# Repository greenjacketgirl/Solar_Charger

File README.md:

# Solar Charger Project

**Introduction** | This project was done in fullfillment of the requirments for Walla Walla University's Power Electronics class (ENGR 460) taught by [Dr. Rob Frohne](https://github.com/frohro). I chose to use Texas Instruments' BQ24650 integrated circuit as the voltage regular between a 11V solar panel and 2s 7.4V lipo. The aim was for the solar panel to charge the lipo battery at 0.5A so as to charge the battery at a standard pace while keeping the pace slow enough that the battery would not be damaged. For more details on the theory used by the charger IC, design specifications, user manual, and more - please reference the [Wiki](https://github.com/greenjacketgirl/Solar_Charger/wiki).

**Navigation** |This repository has content in the [Code](https://github.com/greenjacketgirl/Solar_Charger), [Issues](https://github.com/greenjacketgirl/Solar_Charger/issues), and [Wiki](https://github.com/greenjacketgirl/Solar_Charger/wiki) tabs.The Code section has 1 primary folder - "Solar-Charger" which contains two other folders, "Documentation" and "Kicad". The documentation folder contains stepping stone write ups and research on topics related to the issue as well as my power point presentation on the project. The Kicad folder contains the kicad files, revisions 1 and 2. Note the revisions when you are referencing them. The Wiki page contains the bulk of the documentation for this project which includes, but is not limited to the results, pcb and schematic design motives, specifiations, and objectives for the project. 

**Credits** | This project was chosen and directed by myself. However, I had professional support from my professor [Dr. Rob Frohne](https://github.com/frohro) as well as assistance from the application engineeers at texas instruments. 

**Project Status** | At the current time, the project does not fully work. While the charger circuit does not have any fried or damaged components, it does not charge the lipo battery. The STAT 1 LED turns on, indicating "charging in progress", but no charging has taken place from what I could deduce. See the [Issues](https://github.com/greenjacketgirl/Solar_Charger/issues) page for updates on current bugs.

REV 1: 05/26/2020 Build and Test Stage PART 1 | REV 2: 06/09/2020 Buil and Test Stage PART 2

***
page created by jordyn watkins | greenjacketgirl

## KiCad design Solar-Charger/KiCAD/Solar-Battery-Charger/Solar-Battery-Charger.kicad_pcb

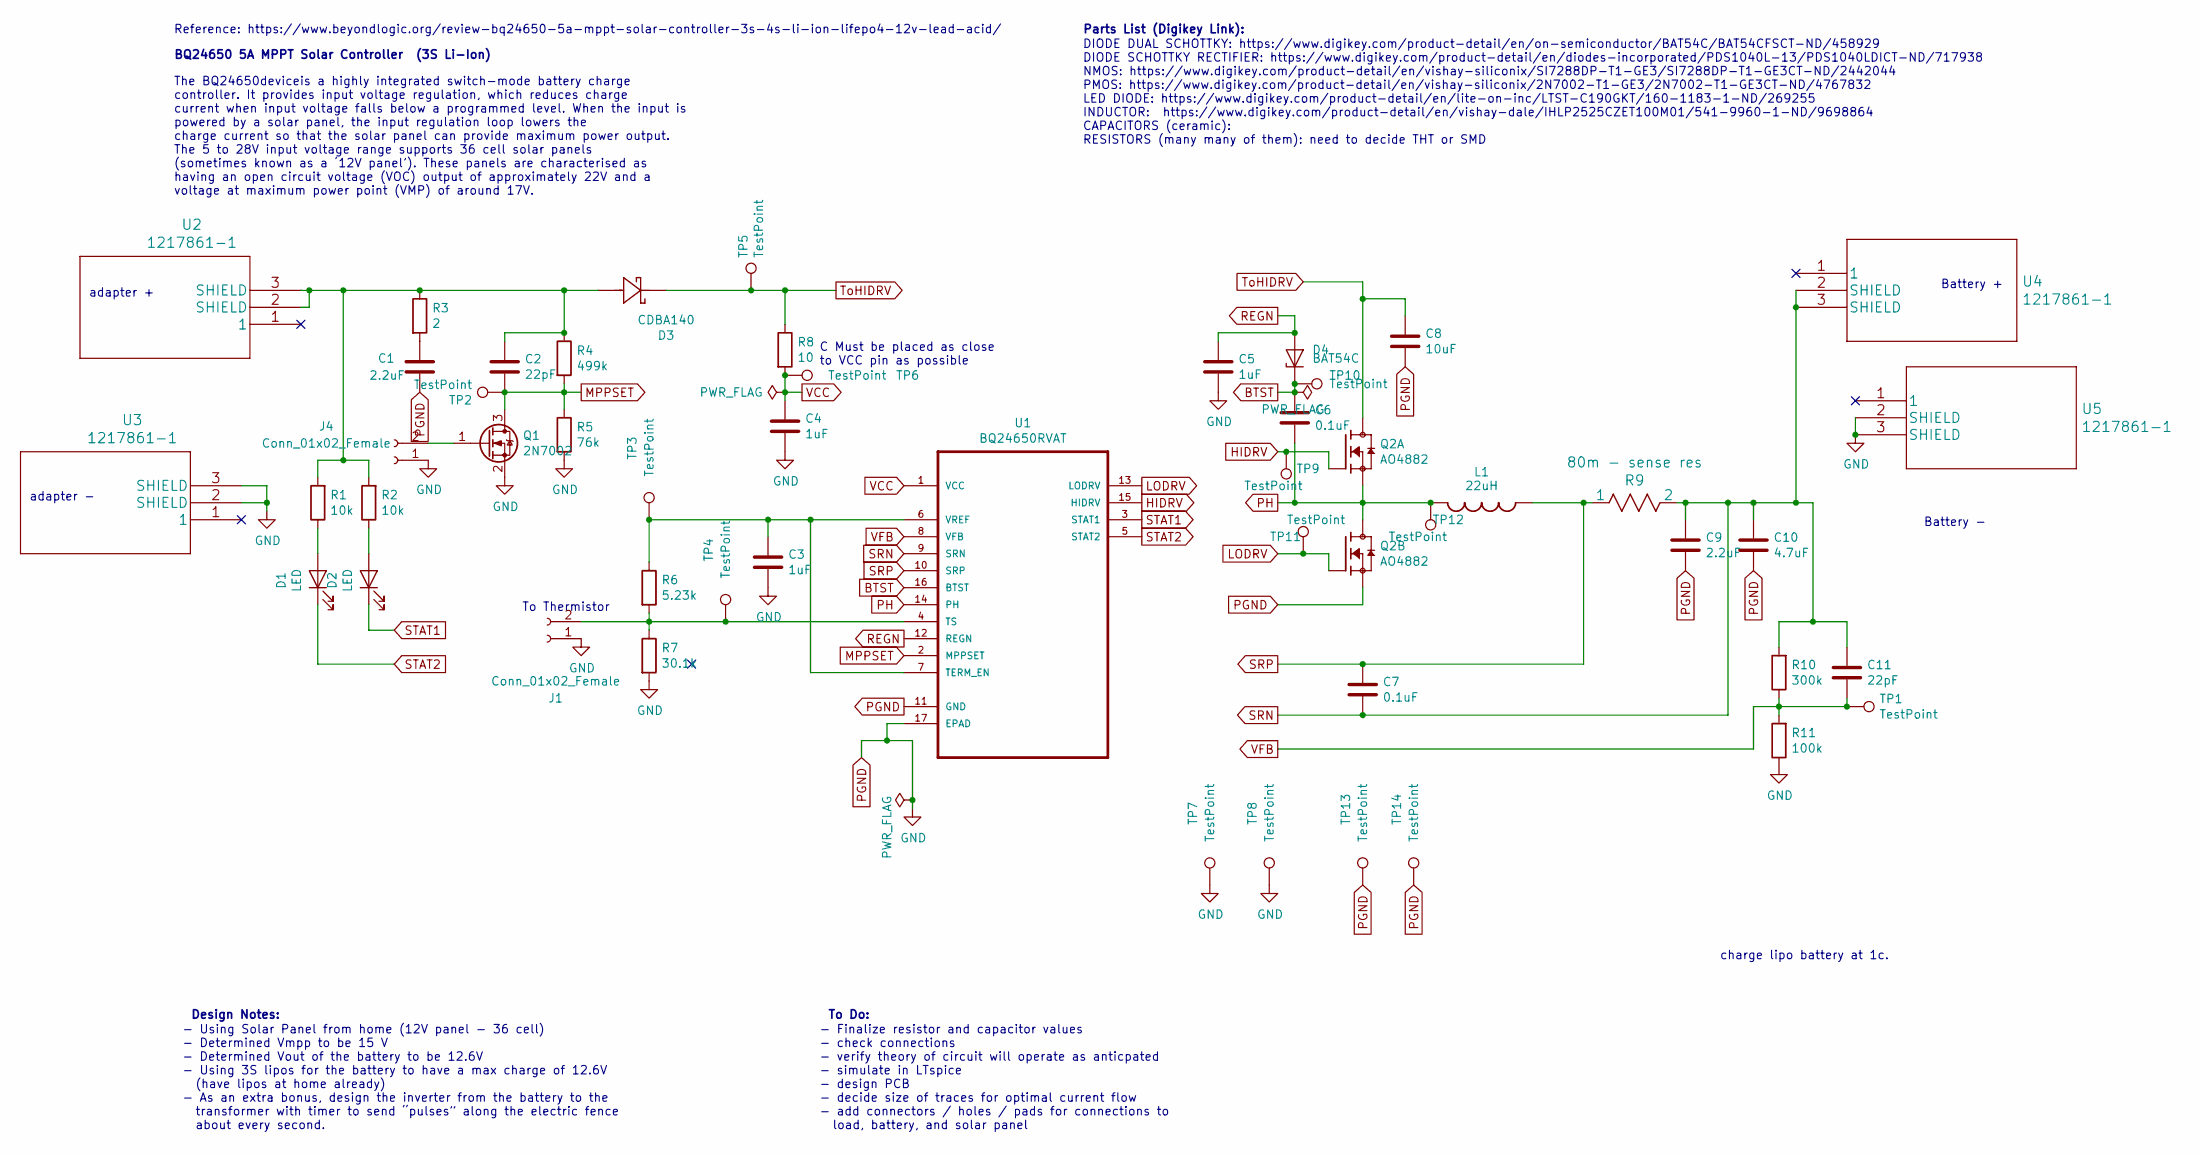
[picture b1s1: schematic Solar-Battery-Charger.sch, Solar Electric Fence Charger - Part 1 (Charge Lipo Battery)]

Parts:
C1, C9: 2.2uF; C_0805_2012Metric
C2, C11: 22pF; C_0805_2012Metric
C3, C4, C5: 1uF; C_0805_2012Metric
C6, C7: 0.1uF; C_0805_2012Metric
C8: 10uF; C_0805_2012Metric
C10: 4.7uF; C_0805_2012Metric
D1, D2: LED; D_0805_2012Metric
D3: CDBA140; CDBA140-G
D4: BAT54C; SOT-23
J1, J4: Conn_01x02_Female; PinSocket_1x02_P2.54mm_Vertical
L1: 22uH; L_0805_2012Metric
Q1: 2N7002; SOT-23
Q2: AO4882; SOIC-8_3.9x4.9mm_P1.27mm
R1, R2: 10k; R_0805_2012Metric
R3: 2; R_0805_2012Metric
R4: 499k; R_0805_2012Metric
R5: 76k; R_0805_2012Metric
R6: 5.23k; R_0805_2012Metric
R7: 30.1k; R_0805_2012Metric
R8: 10; R_0805_2012Metric
R9: 80m - sense res; R_1206_3216Metric
R10: 300k; R_0805_2012Metric
R11: 100k; R_0805_2012Metric
TP1, TP2, TP3, TP4, TP5, TP6, TP7, TP8, TP9, TP10, TP11, TP12, TP13, TP14: TestPoint; TestPoint_Loop_D1.80mm_Drill1.0mm_Beaded
U1: BQ24650RVAT; QFN50P350X350X100-17N
U2, U3, U4, U5: 1217861-1

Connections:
BTST: C6.1, D4.1 (K), TP10.1, U1.16 (BTST)
HIDRV: Q2.4 (G1), TP9.1, U1.15 (HIDRV)
LODRV: Q2.2 (G2), TP11.1, U1.13 (LODRV)
MPPSET: C2.2, Q1.3 (D), R4.2, R5.1, TP2.1, U1.2 (MPPSET)
unnamed: C1.1, R3.2
unnamed: C2.1, D3.2, R1.2, R2.2, R3.1, R4.1, U2.2 (SHIELD), U2.3 (SHIELD)
unnamed: C3.1, R6.1, TP3.1, U1.6 (VREF), U1.7 (TERM_EN)
unnamed: D1.2 (A), R1.1
unnamed: D2.2 (A), R2.1
unnamed: J1.2, R6.2, R7.1, TP4.1, U1.4 (TS)
unnamed: J4.2, Q1.1 (G)
PGND: C1.2, C3.2, C4.2, C5.2, C8.2, C9.1, C10.1, J1.1, J4.1, Q1.2 (S), Q2.1 (S2), R5.2, R7.2, R11.1, TP7.1, TP8.1, TP13.1, TP14.1, U1.11 (GND), U1.17 (EPAD), U3.2 (SHIELD), U3.3 (SHIELD), U5.2 (SHIELD), U5.3 (SHIELD)
PH: C6.2, L1.1, Q2.3 (S1), Q2.7 (D2), Q2.8 (D2), TP12.1, U1.14 (PH)
REGN: C5.1, D4.2 (A), U1.12 (REGN)
SRN: C7.1, C9.2, C10.2, C11.2, R9.2, R10.2, U1.9 (SRN), U4.2 (SHIELD), U4.3 (SHIELD)
SRP: C7.2, L1.2, R9.1, U1.10 (SRP)
STAT1: D2.1 (K), U1.3 (STAT1)
STAT2: D1.1 (K), U1.5 (STAT2)
ToHIDRV: C8.1, D3.1, Q2.5 (D1), Q2.6 (D1), R8.1, TP5.1
VCC: C4.1, R8.2, TP6.1, U1.1 (VCC)
VFB: C11.1, R10.1, R11.2, TP1.1, U1.8 (VFB)

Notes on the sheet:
Reference: https://www.beyondlogic.org/review-bq24650-5a-mppt-solar-controller-3s-4s-li-ion-lifepo4-12v-lead-acid/
Parts List (Digikey Link):
DIODE DUAL SCHOTTKY: https://www.digikey.com/product-detail/en/on-semiconductor/BAT54C/BAT54CFSCT-ND/458929 DIODE SCHOTTKY RECTIFIER: https://www.digikey.com/product-detail/en/diodes-incorporated/PDS1040L-13/PDS1040LDICT-ND/717938 NMOS: https://www.digikey.com/product-detail/en/vishay-siliconix/SI7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
BQ24650 5A MPPT Solar Controller (3S Li-Ion)
The BQ24650deviceis a highly integrated switch-mode battery charge controller. It provides input voltage regulation, which reduces charge current when input voltage falls below a programmed level. When the input is powered by a solar panel, the input regulation loop lowers the charge current so tha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
Design Notes:
- Using Solar Panel from home (12V panel - 36 cell) - Determined Vmpp to be 15 V - Determined Vout of the battery to be 12.6V - Using 3S lipos for the battery to have a max charge of 12.6V (have lipos at home already) - As an extra bonus, design the inverter from the battery to the transformer with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
To Do:
- Finalize resistor and capacitor values - check connections - verify theory of circuit will operate as anticpated - simulate in LTspice - design PCB - decide size of traces for optimal current flow - add connectors / holes / pads for connections to load, battery, and solar panel
charge lipo battery at 1c.
adapter +
C Must be placed as close to VCC pin as possible
Battery +
Battery -
To Thermistor
adapter -

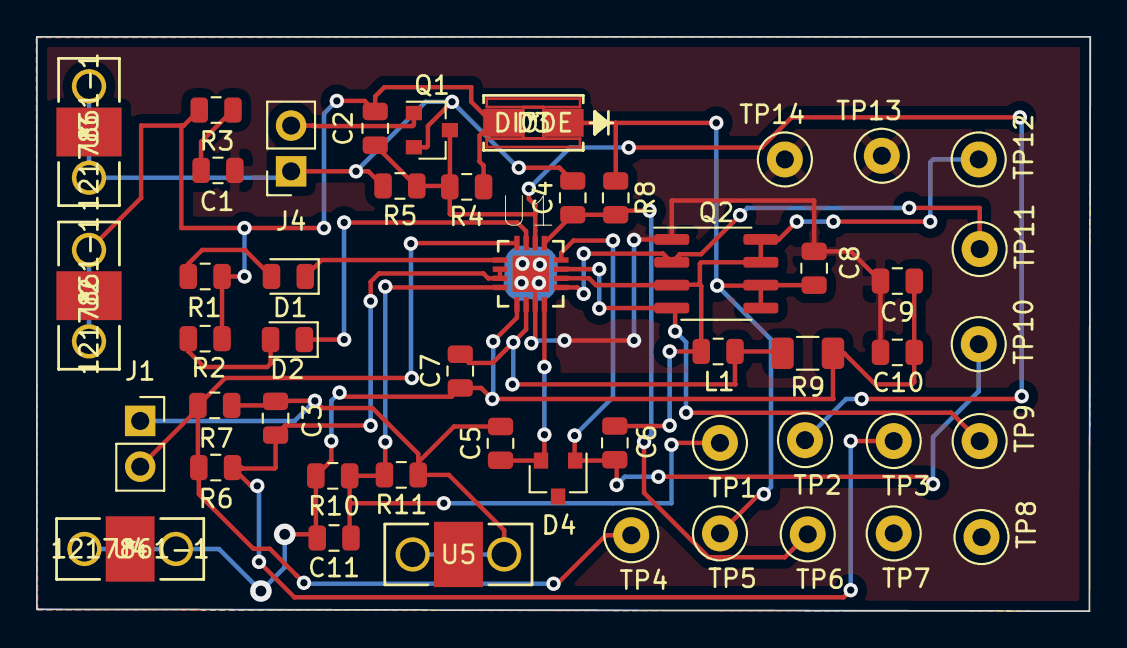
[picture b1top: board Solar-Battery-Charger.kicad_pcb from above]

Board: 2 copper layers, 58.5 x 31.9 mm, 50 parts (0 on the bottom side), 21 nets.

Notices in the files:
parts and their libraries:
Copyright 2016 Accelerated Designs. All rights reserved.
